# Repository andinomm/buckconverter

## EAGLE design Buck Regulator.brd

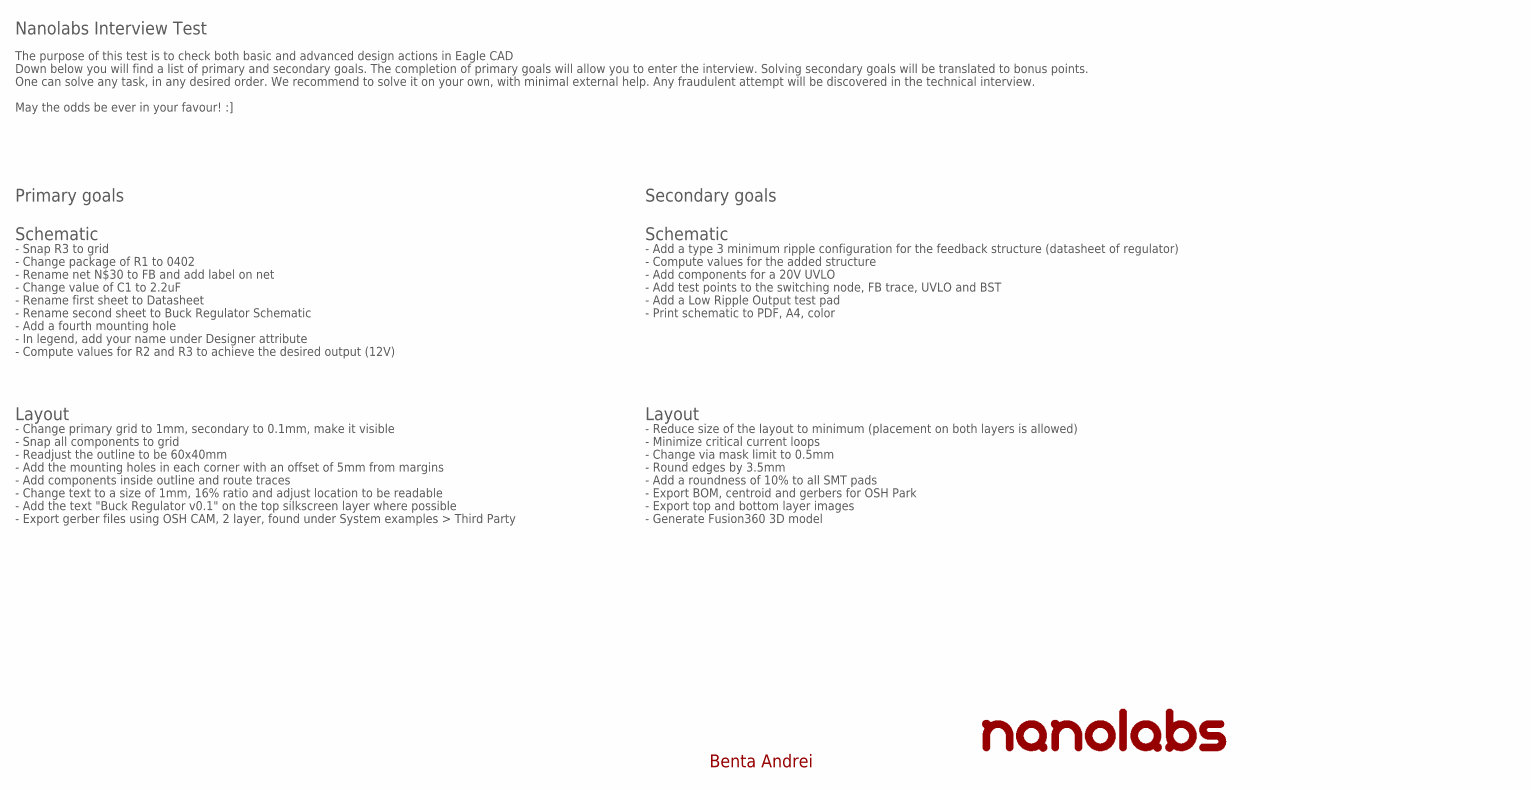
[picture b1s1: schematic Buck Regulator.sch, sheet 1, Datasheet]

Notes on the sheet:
Nanolabs Interview Test
The purpose of this test is to check both basic and advanced design actions in Eagle CAD
Down below you will find a list of primary and secondary goals. The completion of primary goals will allow you to enter the interview. Solving secondary goals will be translated to bonus points.
One can solve any task, in any desired order. We recommend to solve it on your own, with minimal external help. Any fraudulent attempt will be discovered in the technical interview.
May the odds be ever in your favour! :]
Primary goals
Secondary goals
- Snap R3 to grid
- Change package of R1 to 0402
- Rename net N$30 to FB and add label on net
- Rename first sheet to Datasheet
- Rename second sheet to Buck Regulator Schematic
- Add a fourth mounting hole
- In legend, add your name under Designer attribute
- Change value of C1 to 2.2uF
Schematic
- Change primary grid to 1mm, secondary to 0.1mm, make it visible
Layout
- Snap all components to grid
- Readjust the outline to be 60x40mm
- Add the mounting holes in each corner with an offset of 5mm from margins
- Add components inside outline and route traces
- Change text to a size of 1mm, 16% ratio and adjust location to be readable
- Add the text "Buck Regulator v0.1" on the top silkscreen layer where possible
- Export gerber files using OSH CAM, 2 layer, found under System examples > Third Party
- Add a type 3 minimum ripple configuration for the feedback structure (datasheet of regulator)
- Compute values for R2 and R3 to achieve the desired output (12V)
- Compute values for the added structure
- Add components for a 20V UVLO
- Add test points to the switching node, FB trace, UVLO and BST
- Add a Low Ripple Output test pad
- Reduce size of the layout to minimum (placement on both layers is allowed)
- Minimize critical current loops
- Change via mask limit to 0.5mm
- Round edges by 3.5mm
- Add a roundness of 10% to all SMT pads
- Export BOM, centroid and gerbers for OSH Park
- Print schematic to PDF, A4, color
- Export top and bottom layer images
- Generate Fusion360 3D model

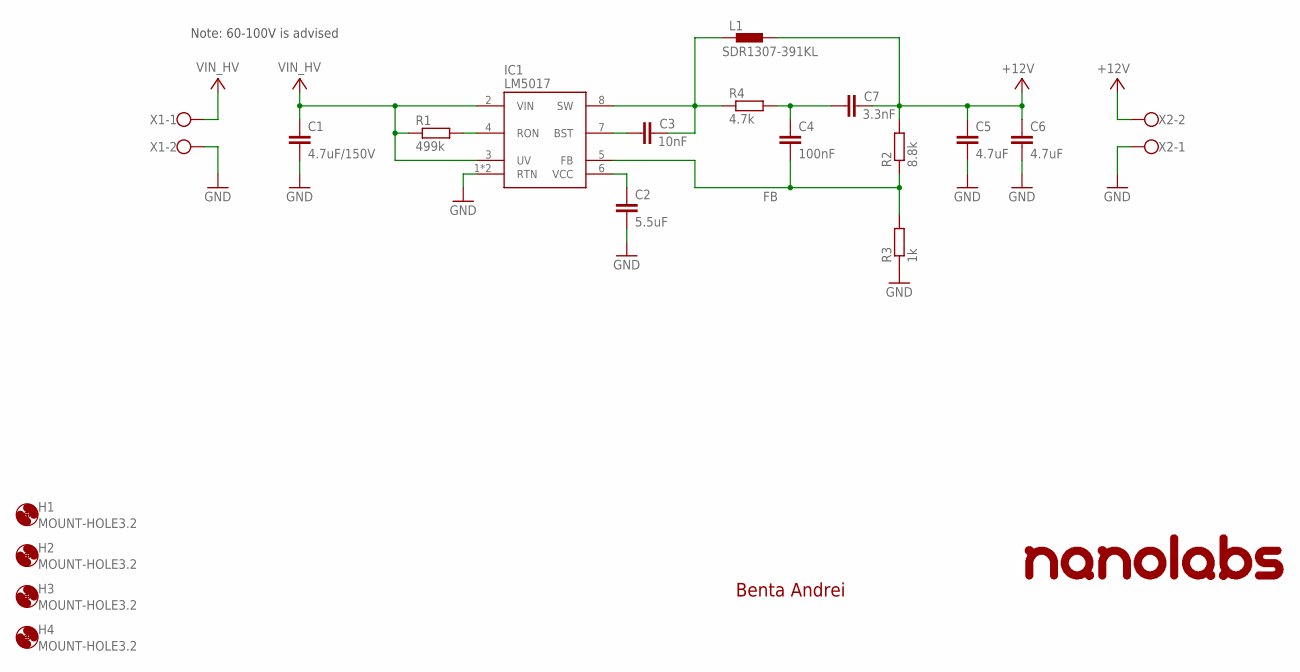
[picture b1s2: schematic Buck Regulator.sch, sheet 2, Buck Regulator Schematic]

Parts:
C1: 4.7uF/150V; C1812
C2: 5.5uF; C0603
C3: 10nF; C0603
C4: 100nF; C0603
C5, C6: 4.7uF; C0603
C7: 3.3nF; C0603
H1, H2, H3, H4: MOUNT-HOLE3.2; 3,2
IC1: LM5017; SO-08-EP
L1: SDR1307-391KL
R1: 499k; R0603
R2: 8.8k; R0603
R3: 1k; R0603
R4: 4.7k; R0603
X1, X2: W237-102

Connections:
+12V: C5.1, C6.1, C7.2, L1.2, R2.2, X2.2
FB: C4.2, IC1.5 (FB), R2.1, R3.2
GND: C1.2, C2.2, C5.2, C6.2, IC1.1 (RTN), IC1.9 (RTN), R3.1, X1.2, X2.1
unnamed: C4.1, C7.1, R4.2
unnamed: C2.1, IC1.6 (VCC)
unnamed: C3.1, IC1.7 (BST)
unnamed: C3.2, IC1.8 (SW), L1.1, R4.1
unnamed: IC1.4 (RON), R1.2
VIN_HV: C1.1, IC1.2 (VIN), IC1.3 (UV), R1.1, X1.1

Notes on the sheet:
Note: 60-100V is advised
Benta Andrei

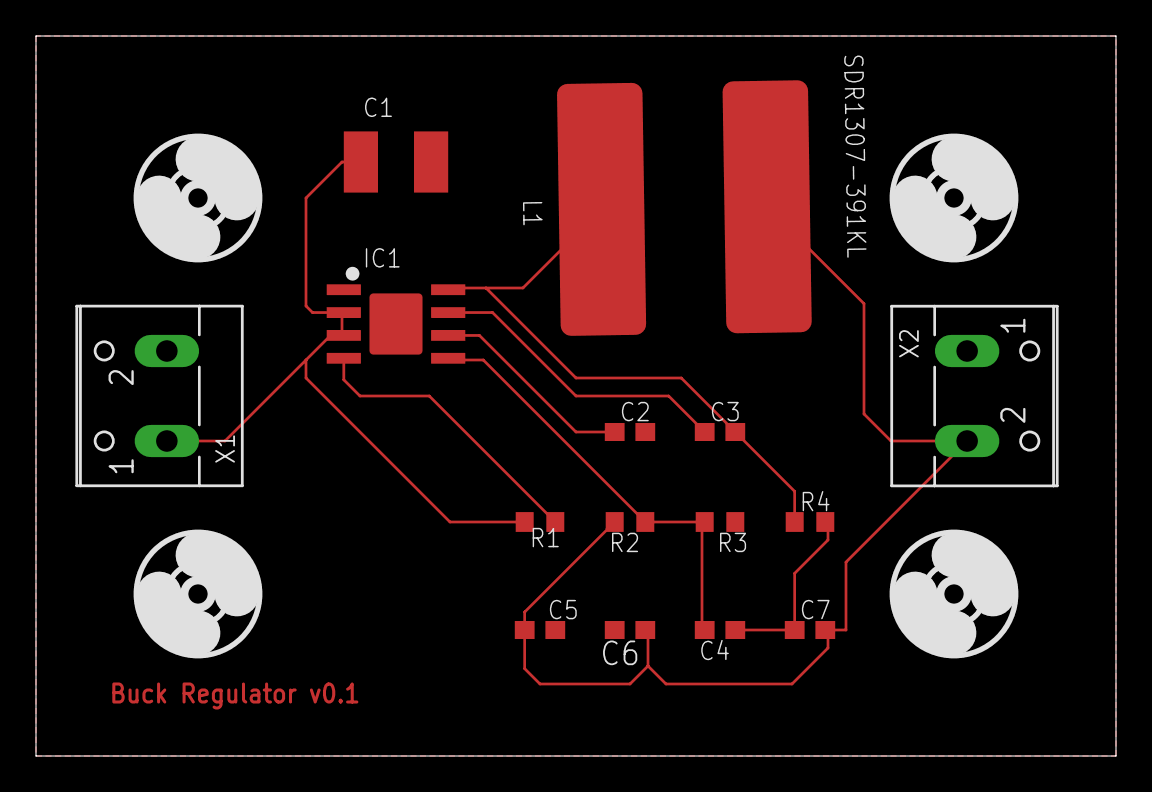
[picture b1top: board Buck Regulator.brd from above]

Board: 2 copper layers, 60.0 x 40.0 mm, 19 parts (0 on the bottom side), 9 nets.
